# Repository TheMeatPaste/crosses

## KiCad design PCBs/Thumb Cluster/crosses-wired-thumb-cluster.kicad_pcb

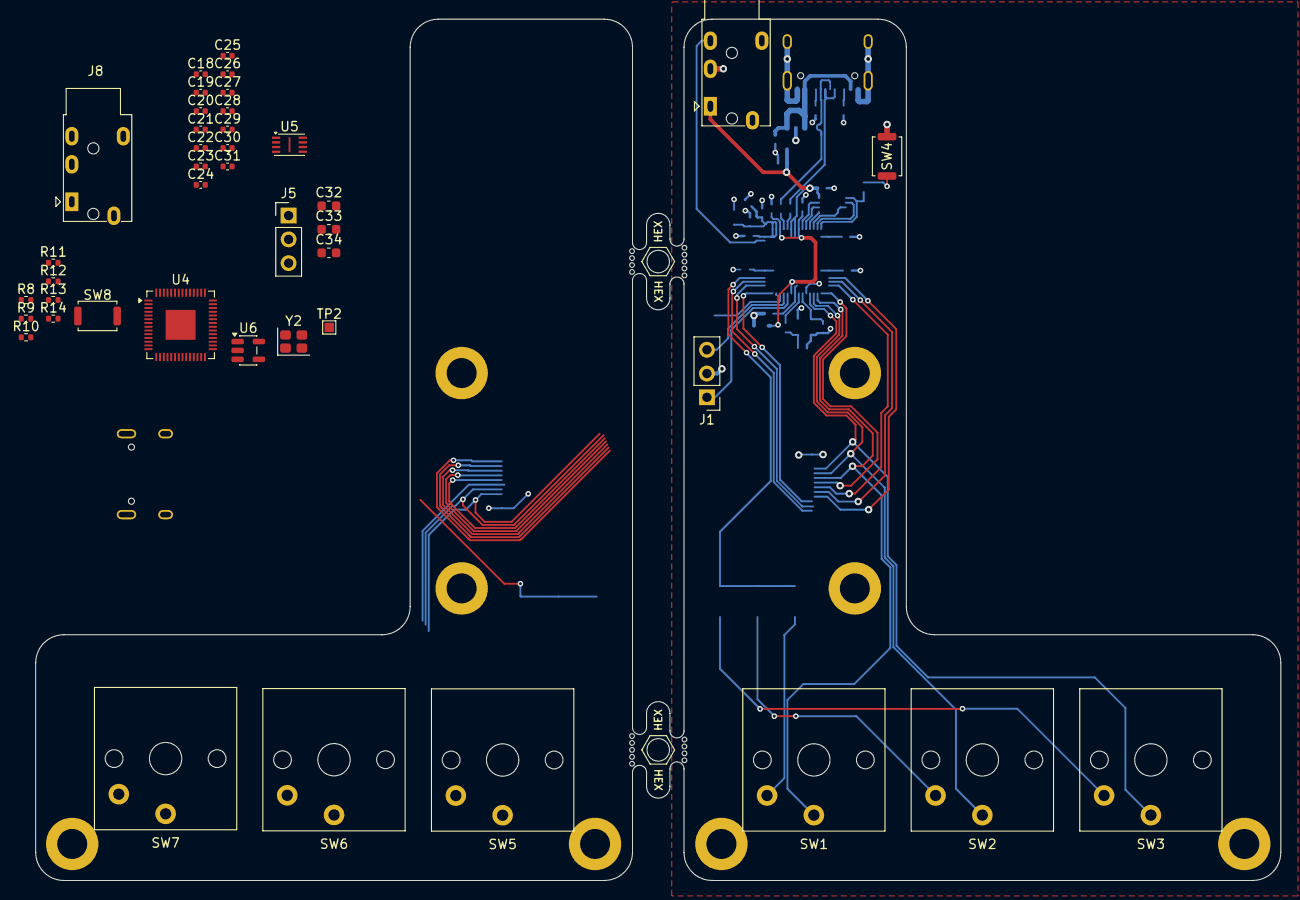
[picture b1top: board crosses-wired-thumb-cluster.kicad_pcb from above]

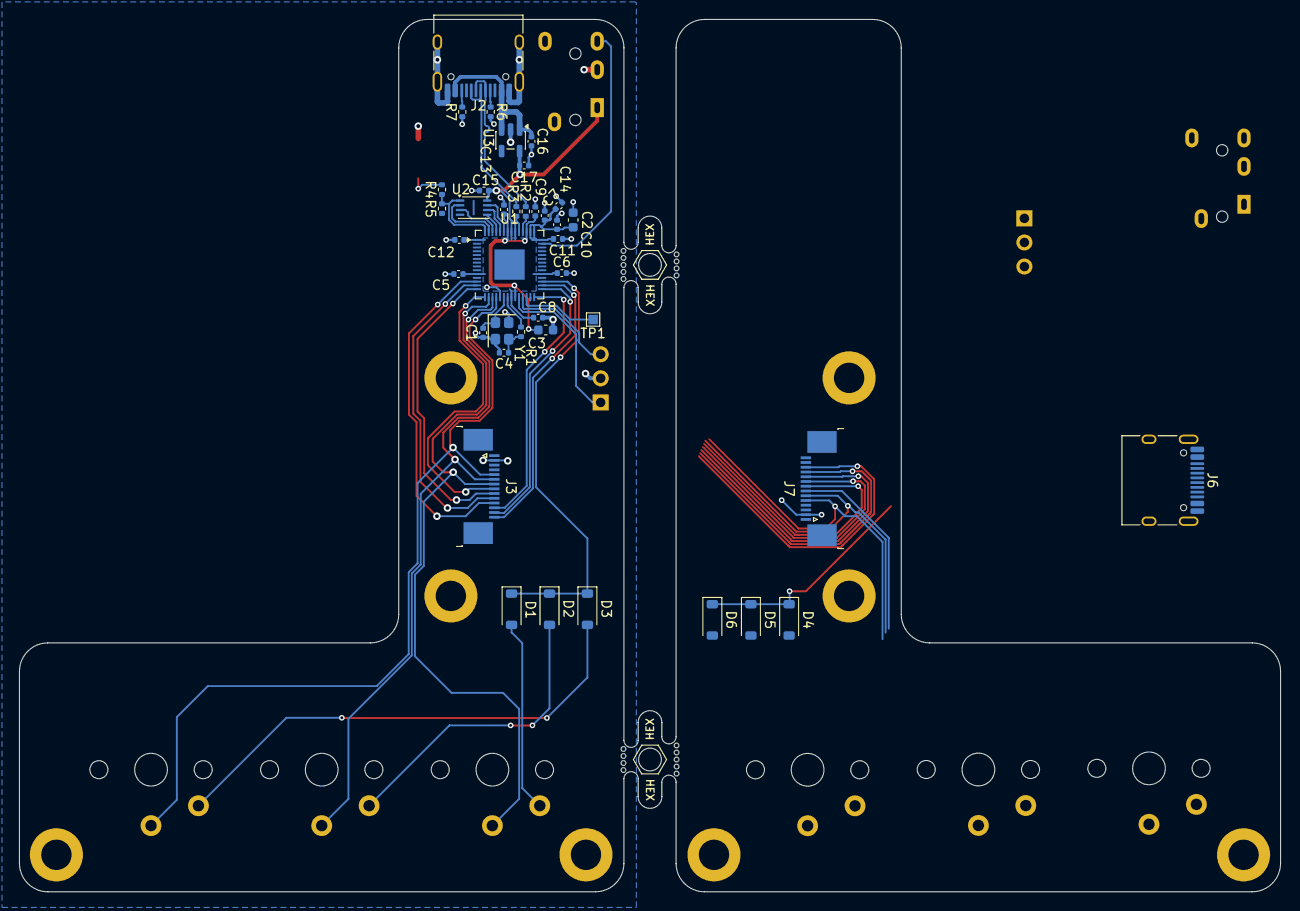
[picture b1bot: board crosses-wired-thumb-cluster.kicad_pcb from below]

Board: 2 copper layers, 133.0 x 92.0 mm, 90 parts (43 on the bottom side), 65 nets.

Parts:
C1, C4, C18, C21: 15pF; C_0402_1005Metric
C2, C3, C32, C33, C34: 1uF; C_0603_1608Metric
C5, C6, C7, C8, C9, C10, C11, C12, C13, C14, C22, C23, C24, C25, C26, C27, C28, C29, C30, C31: 0.1uF; C_0402_1005Metric
C15, C16, C17, C19, C20: 1uF; C_0402_1005Metric
D1, D2, D3, D4, D5, D6: D; D_SOD-123
H1, H2, H3, H4, H5, H6, H7, H8: MountingHole; MountingHole_3.2mm_M3_DIN965_Pad
J1, J5: Conn_01x03; PinHeader_1x03_P2.54mm_Vertical
J2, J6: USB_C_Receptacle_USB2.0_16P; USB_C_Receptacle_HRO_TYPE-C-31-M-12
J3, J7: Conn_01x14_Pin; TE_1-1734839-4_1x14-1MP_P0.5mm_Horizontal
J4, J8: AudioJack4; Jack_3.5mm_PJ320E_Horizontal
MB5, MB5#2: 5.5mm; mousebites_5p5mm_easysnap
R1, R4, R8, R11: 1K; R_0402_1005Metric
R2, R3, R9, R10: 27; R_0402_1005Metric
R5, R12: 10K; R_0402_1005Metric
R6, R7, R13, R14: 5.1K; R_0402_1005Metric
SW1, SW2, SW3, SW5, SW6, SW7: SW_Push; SW_Kailh_Choc_V1_1.00u
SW4, SW8: SW_Push; SW_Push_SPST_NO_Alps_SKRK
TP1, TP2: TestPoint; TestPoint_Pad_1.0x1.0mm
U1, U4: RP2040; QFN-56-1EP_7x7mm_P0.4mm_EP3.2x3.2mm
U2, U5: W25Q128JVS; Winbond_USON-8-1EP_3x2mm_P0.5mm_EP0.2x1.6mm
U3, U6: XC6210B332MR; SOT-23-5
Y1, Y2: Crystal_GND24; Crystal_SMD_2520-4Pin_2.5x2.0mm

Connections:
+1V1-L: C20.1, C30.1, C31.1, U4.23 (DVDD), U4.45 (VREG_VOUT), U4.50 (DVDD)
+1V1-R: C3.1, C13.1, C14.1, U1.23 (DVDD), U1.45 (VREG_VOUT), U1.50 (DVDD)
+3V3-L: C19.1, C22.1, C23.1, C24.1, C25.1, C26.1, C27.1, C28.1, C29.1, C32.1, C34.1, R12.1, U4.1 (IOVDD), U4.10 (IOVDD), U4.22 (IOVDD), U4.33 (IOVDD), U4.42 (IOVDD), U4.43 (ADC_AVDD), U4.44 (VREG_VIN), U4.48 (USB_VDD), U4.49 (IOVDD), U5.8 (VCC), U6.5 (VOUT)
+3V3-R: C2.1, C5.1, C6.1, C7.1, C8.1, C9.1, C10.1, C11.1, C12.1, C15.1, C17.1, J4.T, R5.1, U1.1 (IOVDD), U1.10 (IOVDD), U1.22 (IOVDD), U1.33 (IOVDD), U1.42 (IOVDD), U1.43 (ADC_AVDD), U1.44 (VREG_VIN), U1.48 (USB_VDD), U1.49 (IOVDD), U2.8 (VCC), U3.5 (VOUT)
/L-COL2: J7.5, SW7.1
/L-COL3: J7.6, SW6.1
/L-COL4: J7.7, SW5.1
/L-QSPI_SCLK: U4.52 (QSPI_SCLK), U5.6 (CLK)
/L-QSPI_SD0: U4.53 (QSPI_SD0), U5.5 (DI/IO_{0})
/L-QSPI_SD1: U4.55 (QSPI_SD1), U5.2 (DO/IO_{1})
/L-QSPI_SD2: U4.54 (QSPI_SD2), U5.3 (~WP/IO_{2})
/L-QSPI_SD3: U4.51 (QSPI_SD3), U5.7 (~HOLD/~RESET/IO_{3})
/L-RESET: TP2.1 (1_1), U4.26 (RUN)
/L-ROW3: D4.1 (K), D5.1 (K), D6.1 (K)
/L-SWCLK: J5.1, U4.24 (SWCLK)
/L-SWDI0: J5.3, U4.25 (SWDIO)
/L-USB_DM: J6.A7 (D-), J6.B7 (D-), R9.1
/L-USB_DP: J6.A6 (D+), J6.B6 (D+), R10.2
/R-COL0: J3.9, U1.14 (GPIO11)
/R-COL1: J3.8, U1.15 (GPIO12)
/R-COL2: J3.5, SW3.1, U1.18 (GPIO15)
/R-COL3: J3.6, SW2.1, U1.17 (GPIO14)
/R-COL4: J3.7, SW1.1, U1.16 (GPIO13)
/R-COLP: J3.13, U1.29 (GPIO18)
/R-QSPI_SCLK: U1.52 (QSPI_SCLK), U2.6 (CLK)
/R-QSPI_SD0: U1.53 (QSPI_SD0), U2.5 (DI/IO_{0})
/R-QSPI_SD1: U1.55 (QSPI_SD1), U2.2 (DO/IO_{1})
/R-QSPI_SD2: U1.54 (QSPI_SD2), U2.3 (~WP/IO_{2})
/R-QSPI_SD3: U1.51 (QSPI_SD3), U2.7 (~HOLD/~RESET/IO_{3})
/R-QSPI_SS: R4.2, R5.2, R11.2, R12.2, U1.56 (~QSPI_SS), U2.1 (~CS), U5.1 (~CS)
/R-RESET: TP1.1 (1_1), U1.26 (RUN)
/R-ROW0: J3.10, U1.13 (GPIO10)
/R-ROW1: J3.11, U1.12 (GPIO9)
/R-ROW2: J3.12, U1.28 (GPIO17)
/R-ROW3: D1.1 (K), D2.1 (K), D3.1 (K), U1.31 (GPIO20)
/R-ROWH: J3.14, U1.30 (GPIO19)
/R-SERIAL: J4.R2, U1.41 (GPIO29/ADC3)
/R-SWCLK: J1.1, U1.24 (SWCLK)
/R-SWDI0: J1.3, U1.25 (SWDIO)
/R-USB_DN: J2.A7 (D-), J2.B7 (D-), R2.1, R2.2, U1.46 (USB_DM)
/R-USB_DP: J2.A6 (D+), J2.B6 (D+), R3.1, R3.2, U1.47 (USB_DP)
GND-L: C18.2, C19.2, C20.2, C21.2, C22.2, C23.2, C24.2, C25.2, C26.2, C27.2, C28.2, C29.2, C30.2, C31.2, C32.2, C33.2, C34.2, J5.2, J6.A1 (GND), J6.A12 (GND), J6.B1 (GND), J6.B12 (GND), J6.SH (SHIELD), J7.2, J8.R1, R13.2, R14.1, SW8.1, U4.19 (TESTEN), U4.57 (GND), U5.4 (GND), U6.2 (GND), Y2.2 (G), Y2.4 (G)
GND-R: C1.2, C2.2, C3.2, C4.2, C5.2, C6.2, C7.2, C8.2, C9.2, C10.2, C11.2, C12.2, C13.2, C14.2, C15.2, C16.2, C17.2, J1.2, J2.A1 (GND), J2.A12 (GND), J2.B1 (GND), J2.B12 (GND), J2.SH (SHIELD), J3.2, J4.R1, R6.2, R7.1, SW4.1, U1.19 (TESTEN), U1.57 (GND), U2.4 (GND), U3.2 (GND), Y1.2 (G), Y1.4 (G)
unnamed: C4.1, R1.1, Y1.3
unnamed: C21.1, R8.1, Y2.3
unnamed: D1.2 (A), SW1.2
unnamed: D2.2 (A), SW2.2
unnamed: D3.2 (A), SW3.2
unnamed: D4.2 (A), SW5.2
unnamed: D5.2 (A), SW6.2
unnamed: D6.2 (A), SW7.2
unnamed: J2.A5 (CC1), R6.1
unnamed: J2.B5 (CC2), R7.2
unnamed: J6.A5 (CC1), R13.1
unnamed: J6.B5 (CC2), R14.2
unnamed: R4.1, SW4.2
unnamed: R11.1, SW8.2
unnamed: C1.1, U1.20 (XIN), Y1.1
unnamed: R1.2, U1.21 (XOUT)
unnamed: R9.2, U4.46 (USB_DM)
unnamed: R10.1, U4.47 (USB_DP)
unnamed: C18.1, U4.20 (XIN), Y2.1
unnamed: R8.2, U4.21 (XOUT)
VBUS-L: C33.1, J6.A4 (VBUS), J6.A9 (VBUS), J6.B4 (VBUS), J6.B9 (VBUS), U6.1 (VIN), U6.3 (CE)
VBUS-R: C16.1, J2.A4 (VBUS), J2.A9 (VBUS), J2.B4 (VBUS), J2.B9 (VBUS), U3.1 (VIN), U3.3 (CE)

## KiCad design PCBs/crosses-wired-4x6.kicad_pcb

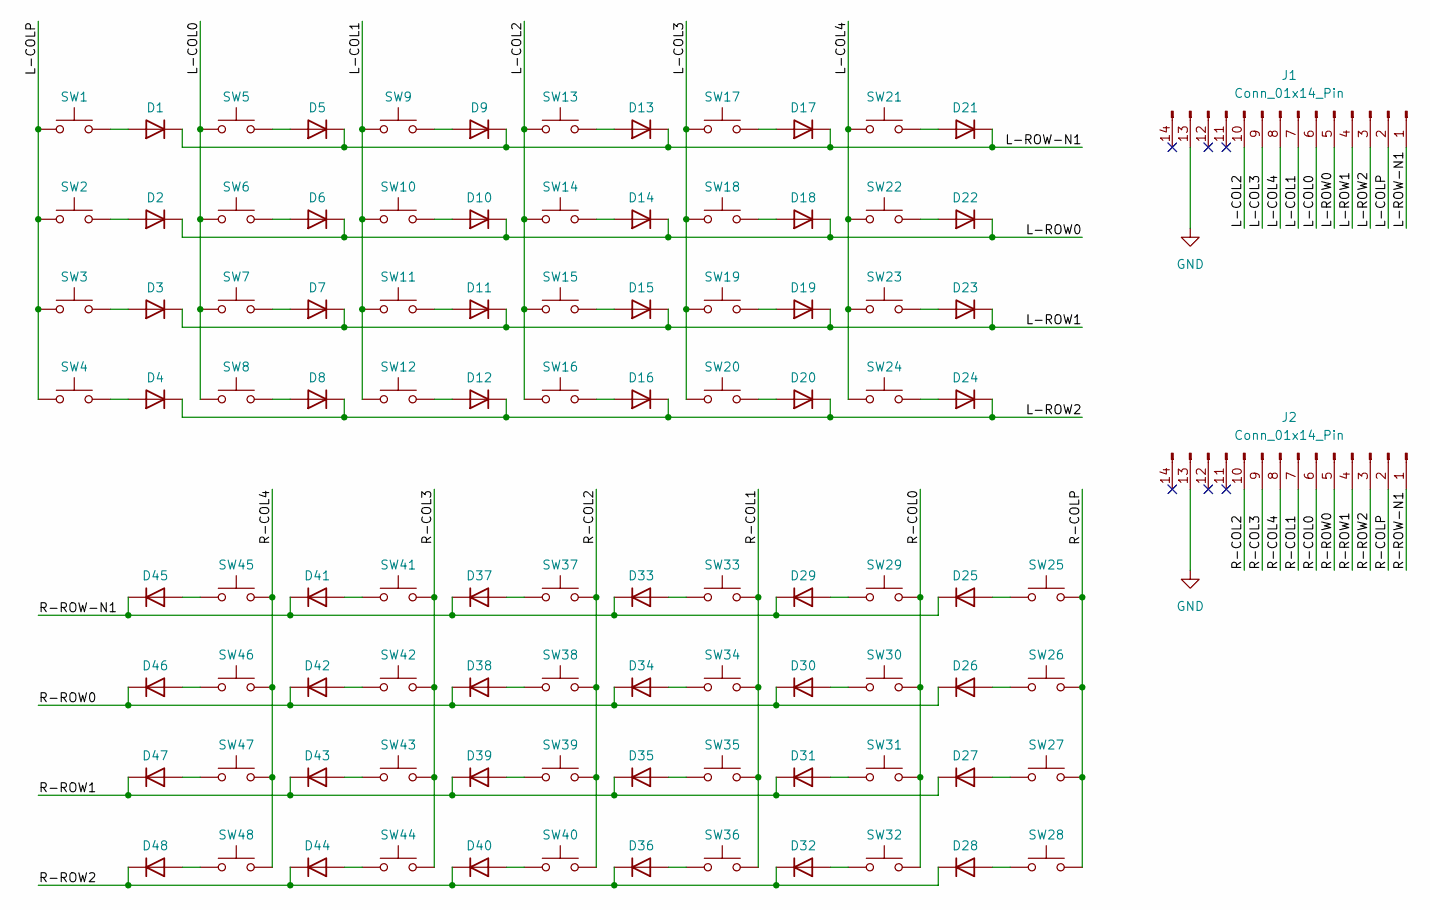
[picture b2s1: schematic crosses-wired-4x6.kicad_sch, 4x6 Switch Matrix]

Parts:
D1, D2, D3, D4, D5, D6, D7, D8, D9, D10, D11, D12, D13, D14, D15, D16, D17, D18, D19, D20, D21, D22, D23, D24, D25, D26, D27, D28, D29, D30, D31, D32, D33, D34, D35, D36, D37, D38, D39, D40, D41, D42, D43, D44, D45, D46, D47, D48: D
J1, J2: Conn_01x14_Pin
SW1, SW2, SW3, SW4, SW5, SW6, SW7, SW8, SW9, SW10, SW11, SW12, SW13, SW14, SW15, SW16, SW17, SW18, SW19, SW20, SW21, SW22, SW23, SW24, SW25, SW26, SW27, SW28, SW29, SW30, SW31, SW32, SW33, SW34, SW35, SW36, SW37, SW38, SW39, SW40, SW41, SW42, SW43, SW44, SW45, SW46, SW47, SW48: SW_Push

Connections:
/L-COL0: J1.6, SW5.1, SW6.1, SW7.1, SW8.1
/L-COL1: J1.7, SW9.1, SW10.1, SW11.1, SW12.1
/L-COL2: J1.10, SW13.1, SW14.1, SW15.1, SW16.1
/L-COL3: J1.9, SW17.1, SW18.1, SW19.1, SW20.1
/L-COL4: J1.8, SW21.1, SW22.1, SW23.1, SW24.1
/L-COLP: J1.2, SW1.1, SW2.1, SW3.1, SW4.1
/L-ROW0: D2.1 (K), D6.1 (K), D10.1 (K), D14.1 (K), D18.1 (K), D22.1 (K), J1.5
/L-ROW1: D3.1 (K), D7.1 (K), D11.1 (K), D15.1 (K), D19.1 (K), D23.1 (K), J1.4
/L-ROW2: D4.1 (K), D8.1 (K), D12.1 (K), D16.1 (K), D20.1 (K), D24.1 (K), J1.3
/L-ROW-N1: D1.1 (K), D5.1 (K), D9.1 (K), D13.1 (K), D17.1 (K), D21.1 (K), J1.1
/R-COL0: J2.6, SW29.1, SW30.1, SW31.1, SW32.1
/R-COL1: J2.7, SW33.1, SW34.1, SW35.1, SW36.1
/R-COL2: J2.10, SW37.1, SW38.1, SW39.1, SW40.1
/R-COL3: J2.9, SW41.1, SW42.1, SW43.1, SW44.1
/R-COL4: J2.8, SW45.1, SW46.1, SW47.1, SW48.1
/R-COLP: J2.2, SW25.1, SW26.1, SW27.1, SW28.1
/R-ROW0: D26.1 (K), D30.1 (K), D34.1 (K), D38.1 (K), D42.1 (K), D46.1 (K), J2.5
/R-ROW1: D27.1 (K), D31.1 (K), D35.1 (K), D39.1 (K), D43.1 (K), D47.1 (K), J2.4
/R-ROW2: D28.1 (K), D32.1 (K), D36.1 (K), D40.1 (K), D44.1 (K), D48.1 (K), J2.3
/R-ROW-N1: D25.1 (K), D29.1 (K), D33.1 (K), D37.1 (K), D41.1 (K), D45.1 (K), J2.1
GND: J1.13, J2.13
unnamed: D1.2 (A), SW1.2
unnamed: D2.2 (A), SW2.2
unnamed: D3.2 (A), SW3.2
unnamed: D4.2 (A), SW4.2
unnamed: D5.2 (A), SW5.2
unnamed: D6.2 (A), SW6.2
unnamed: D7.2 (A), SW7.2
unnamed: D8.2 (A), SW8.2
unnamed: D9.2 (A), SW9.2
unnamed: D10.2 (A), SW10.2
unnamed: D11.2 (A), SW11.2
unnamed: D12.2 (A), SW12.2
unnamed: D13.2 (A), SW13.2
unnamed: D14.2 (A), SW14.2
unnamed: D15.2 (A), SW15.2
unnamed: D16.2 (A), SW16.2
unnamed: D17.2 (A), SW17.2
unnamed: D18.2 (A), SW18.2
unnamed: D19.2 (A), SW19.2
unnamed: D20.2 (A), SW20.2
unnamed: D21.2 (A), SW21.2
unnamed: D22.2 (A), SW22.2
unnamed: D23.2 (A), SW23.2
unnamed: D24.2 (A), SW24.2
unnamed: D25.2 (A), SW25.2
unnamed: D26.2 (A), SW26.2
unnamed: D27.2 (A), SW27.2
unnamed: D28.2 (A), SW28.2
unnamed: D29.2 (A), SW29.2
unnamed: D30.2 (A), SW30.2
unnamed: D31.2 (A), SW31.2
unnamed: D32.2 (A), SW32.2
unnamed: D33.2 (A), SW33.2
unnamed: D34.2 (A), SW34.2
unnamed: D35.2 (A), SW35.2
unnamed: D36.2 (A), SW36.2
unnamed: D37.2 (A), SW37.2
unnamed: D38.2 (A), SW38.2
unnamed: D39.2 (A), SW39.2
unnamed: D40.2 (A), SW40.2
unnamed: D41.2 (A), SW41.2
unnamed: D42.2 (A), SW42.2
unnamed: D43.2 (A), SW43.2
unnamed: D44.2 (A), SW44.2
unnamed: D45.2 (A), SW45.2
unnamed: D46.2 (A), SW46.2
unnamed: D47.2 (A), SW47.2
unnamed: D48.2 (A), SW48.2

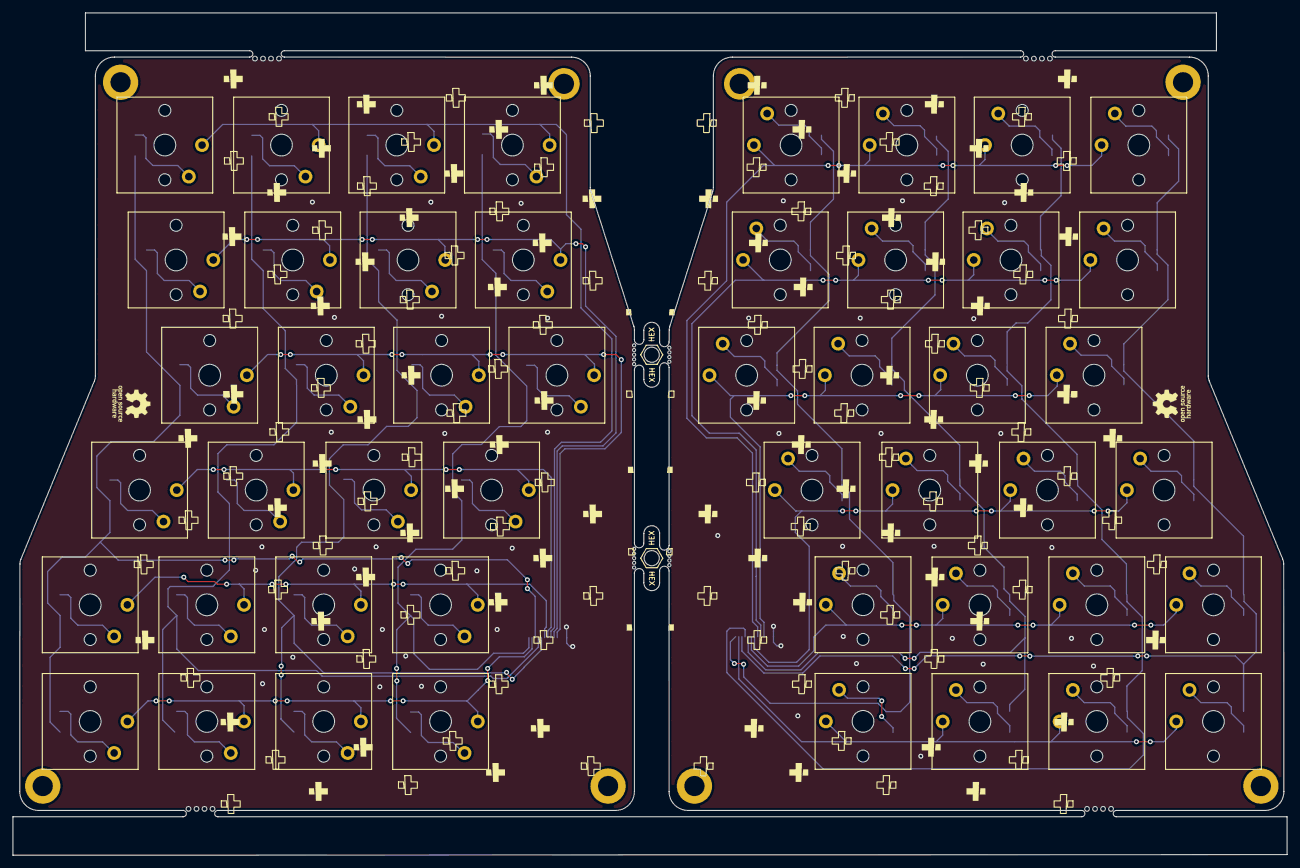
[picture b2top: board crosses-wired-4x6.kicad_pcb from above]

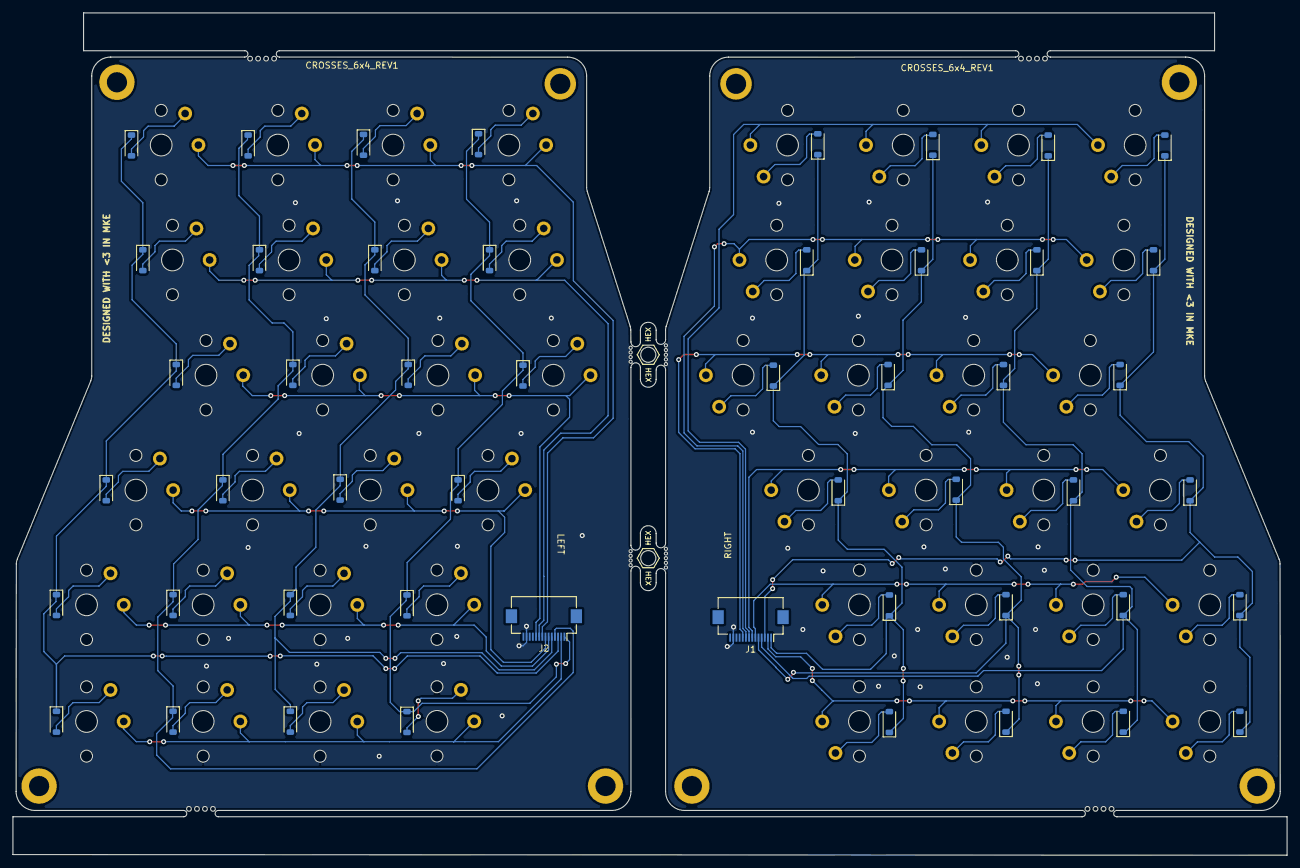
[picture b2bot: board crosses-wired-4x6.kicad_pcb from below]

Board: 2 copper layers, 202.1 x 133.6 mm, 108 parts (54 on the bottom side), 69 nets.

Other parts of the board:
H1, H1#2, H3, H3#2, H5, H5#2, H6, H6#2: MountingHole; MountingHole_3.2mm_M3_DIN965_Pad
MB5, MB5#2: 5.5mm; mousebites_5p5mm_easysnap

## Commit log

2026-04-09 Removed OLED headers and traces
2026-04-09 Added schematic | Updated PCB references
2026-04-10 Switched to non-hotswap footprints | Rerouted board for new switch footprints
2026-04-10 Added gitignore | Reorganized project structure
2026-04-12 Added a project | Addded a Schematic | Started the board routing
2026-04-17 Finished routing right side thumb cluster
